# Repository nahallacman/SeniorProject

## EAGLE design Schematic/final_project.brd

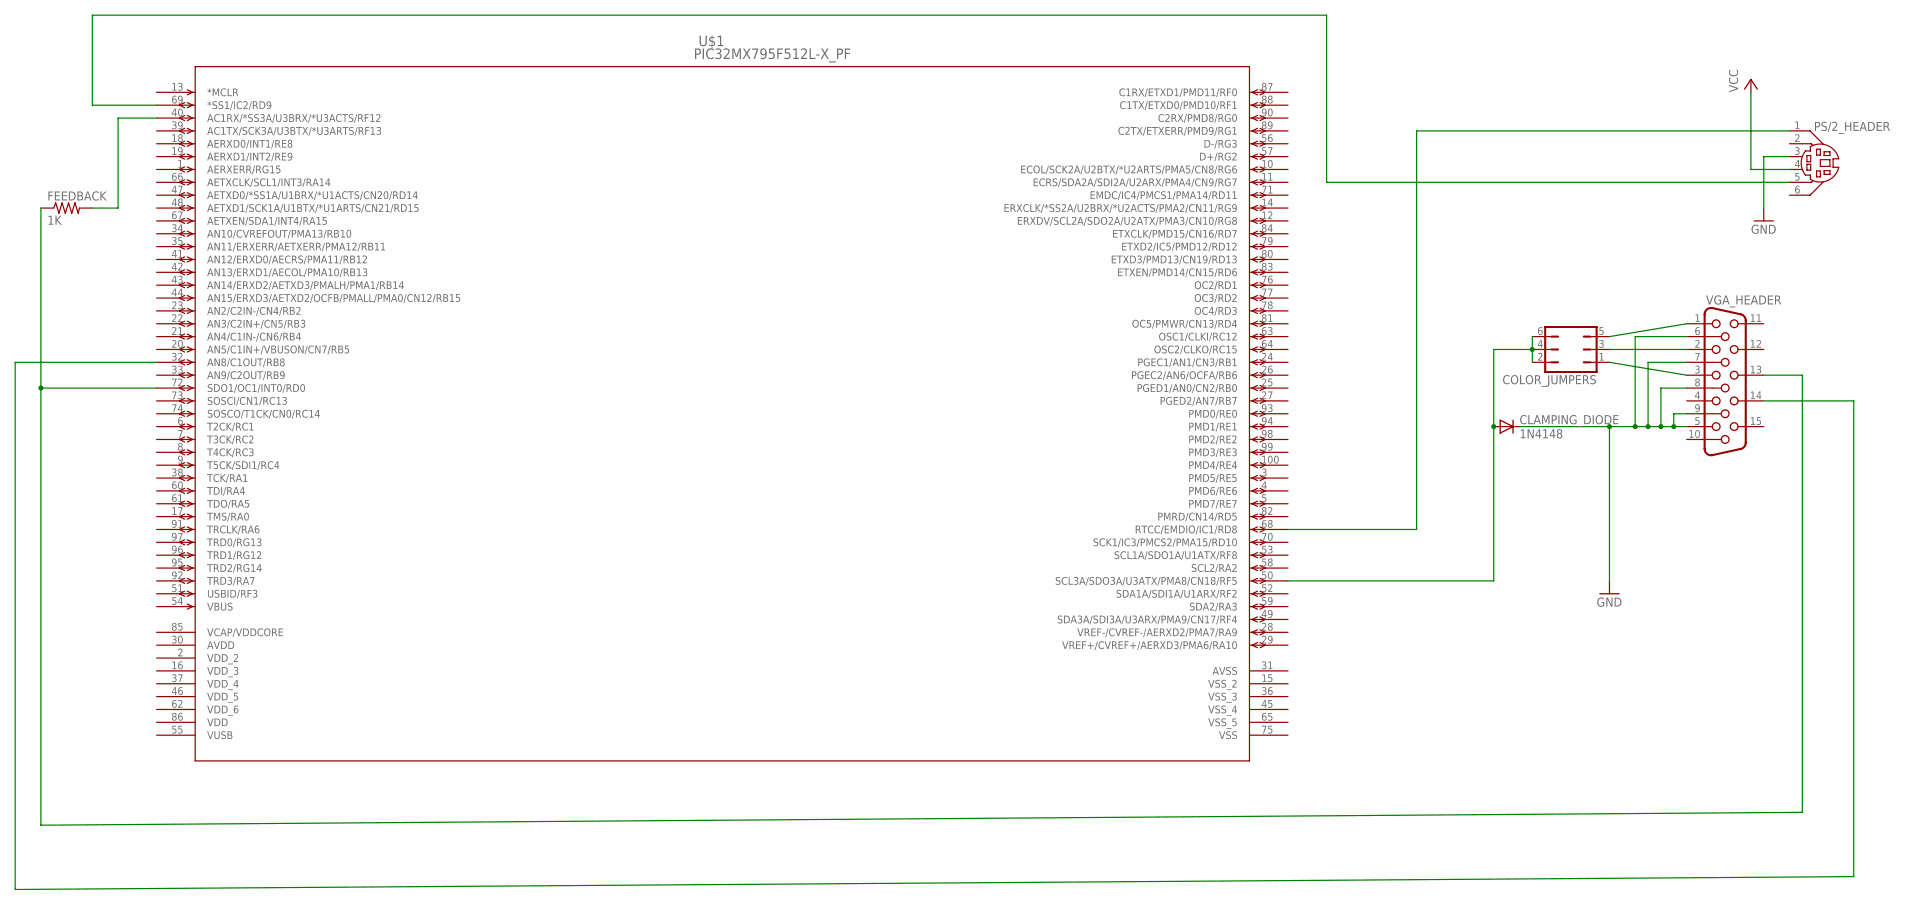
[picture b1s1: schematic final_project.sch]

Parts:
CLAMPING_DIODE: 1N4148; DO41-10
COLOR_JUMPERS: JP3Q
FEEDBACK: 1K; 0204V
PS/2_HEADER: MDIN06K
U$1: PIC32MX795F512L-X_PF; TQFP100_14X14MC
VGA_HEADER: HF15H; HDF15H

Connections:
AVDD: U$1.30 (AVDD)
AVSS: U$1.31 (AVSS)
GND: CLAMPING_DIODE.C, PS/2_HEADER.3, VGA_HEADER.5, VGA_HEADER.6, VGA_HEADER.7, VGA_HEADER.8, VGA_HEADER.9
unnamed: COLOR_JUMPERS.5, VGA_HEADER.1
unnamed: COLOR_JUMPERS.3, VGA_HEADER.2
unnamed: COLOR_JUMPERS.1, VGA_HEADER.3
unnamed: CLAMPING_DIODE.A, COLOR_JUMPERS.2, COLOR_JUMPERS.4, COLOR_JUMPERS.6, U$1.50 (SCL3A/SDO3A/U3ATX/PMA8/CN18/RF5)
unnamed: U$1.32 (AN8/C1OUT/RB8), VGA_HEADER.14
unnamed: FEEDBACK.1, VGA_HEADER.13
unnamed: PS/2_HEADER.1, U$1.68 (RTCC/EMDIO/IC1/RD8)
unnamed: PS/2_HEADER.5, U$1.69 (*SS1/IC2/RD9)
unnamed: FEEDBACK.2, U$1.40 (AC1RX/*SS3A/U3BRX/*U3ACTS/RF12)
VCAP/VDDCORE: U$1.85 (VCAP/VDDCORE)
VCC: PS/2_HEADER.4
VDD: U$1.86 (VDD)
VDD_2: U$1.2 (VDD_2)
VDD_3: U$1.16 (VDD_3)
VDD_4: U$1.37 (VDD_4)
VDD_5: U$1.46 (VDD_5)
VDD_6: U$1.62 (VDD_6)
VSS: U$1.75 (VSS)
VSS_2: U$1.15 (VSS_2)
VSS_3: U$1.36 (VSS_3)
VSS_4: U$1.45 (VSS_4)
VSS_5: U$1.65 (VSS_5)
VUSB: U$1.55 (VUSB)

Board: 2 copper layers, 6 parts (0 on the bottom side), 10 nets, no tracks yet.

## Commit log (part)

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2014-09-14 :circus_tent: Added .gitattributes & .gitignore files
2014-09-21 TCP client and server demos working
2014-10-27 Keyboard demo working
    Keyboard shows clock state change using breakpoints, demonstrates that
    the keyboard is sending a clock signal.
2014-11-15 Testing variation 2
    Got the screen to blink on and off while trying, probably closer to the
    correct timing. To get any other real meaningful changes I will probably
    need a logic analyzer or an oscilloscope. Probably the oscilloscope for
    the levels I am using, .7 volts is VGA standard.
2014-11-16 small edits
2014-11-25 Quick ISR rewrite
    Not tested. Left old test file as oldmain.c, replaced the main,c with a
    new one with ISR's in it.
2014-11-25 ISR's working, needs testing
2014-11-26 self modifying ISR's
2014-12-12 Working Senior Project Demo
    Begins by displaying a single line on screen. On any key press it
    changes to display 3 lines.
2014-12-18 More configuration tinkering
    Still can't get the SPI interrupt to fire correctly, probably need to
    find the exact documentation for my processor.
2014-12-18 more testing
    trying to get SPI to transmit, can't seem to get that to happen, but now
    the interrupt properly happens at least,.
2014-12-19 Alright solid lines
    H-sync is still off, not sure what the actual resolution being displayed
    is.
2014-12-20 Much more solid lines
    Not perfect yet, but the lines are no longer incredibly shaky.
2014-12-20 most solid lines so far
    but not quite complete.
2014-12-20 minor testing
    Hardware may be causing current sourcing problems, all 5's don't display
    properly.
2014-12-26 writechar() works minimally
    writechar() is able to take an 8 character array and display it over 8
    lines while taking an x and y co-ordinate. The y co-ordinate is exact,
    but the x co-ordinate only rounds to 32 bit numbers which needs to be
    fixed.
2014-12-26 Cleaned up main.c
    Put several items into the VGA.c/.h files where they belong, system
    confirmed to still work.
2015-01-12 Change Notification Interrupt works
    The interrupt fires correctly, but the ISR doesn't properly read the key
    press.
2015-01-19 Keyboard Scan Code Buffer works
    Multiple key presses and releases are confirmed working and values are
    correctly written into the buffer.
2015-01-19 Messing with writechar()
    Still doesn't work correctly. Will attempt again another day.
2015-01-20 Tied key presses to printing
    Took a bit of messing with things and using an external variable to tell
    the system when a keypress is ready to be processed. Screen will change
    when a key is pressed on the keyboard.
2015-01-20 Added a few characters to be translated
    will now print "q w e r t y"
2015-01-24 Added most of the normal keys.
    They all print, every character that is implemented currently is:
    `1234567890-=qwertyuiop[]\asdfghjkl;'zxcvbnm,./
    Still needed are F# keys, num pad keys, modifier keys, arrow keys, ect.
2015-01-28 Laptop Updates
2015-01-30 testing
2015-01-31 Fixed screen garbage!
    writechar() has been fixed, screen correctly prints all characters now.
2015-01-31 Added descriptive comments about future work
2015-02-01 Added ShiftScreenDown() to VGA.c
    Now I have a screen that scrolls up and and down, next I might go for
    right or left, even though that is not as important. Going to put that
    into the maybe category.
2015-02-02 Added basic Caps Lock functionality
    Caps lock inverts shift on/off. Left shift turns shift on, right shift
    turns shift off. Also added all the ~!@#$%^&*()_+ symbols to be printed.
2015-02-05 Added line input base and cursor limiting
    Added a new function placeChar() to wrap writechar() and control where
    things are on the screen. Needs work with the line in the cases of
    having text before the line starts, and accumulating the line. A good
    way to do accumulation is fill the line buffer, then copy it when you
    hit enter.
2015-02-08 Moved PS/2 to other port pins
    Now using input comparator 2 for PS/2.
2015-02-18 comment fix and added pictures
2015-02-27 Got the Ethernet starter kit working
    Got it working with a python demo that prints the text that it receives
    from a single source. Tested from other computers and the same computer
    using putty. Doesn't currently work from same computer, only the name
    192.168.11.57 so make sure to change that if you can't get listening
    working.
2015-03-03 editor changes
2015-03-03 Made text send over TCP/IP!!!!1
    It sends text, but at the end of a keypress( not too sure why).
    Regardless, I am able to enter in text on a keyboard, display it on a
    screen, and send it over TCP/IP, the three major goals in my project.
2015-03-04 Altered escape, clears screen, resets cursor
2015-03-07 Added PS2.c updates
    Forgot to add those.
2015-03-07 Finished the __Microcontroller defines
    Should keep the test code base and the pic32 only code base separate
    now.
2015-03-07 Changed the includes, needs to be tested
2015-03-07 Problems with default global values
    Need to alter all of the code to remove default global values, but it
    should be done incrementally. Going to test these changes so far then
    add more changes.
2015-03-07 Few alterations, working on hardware
2015-03-08 Tried hard links fixes.
    Seems to have worked. Will see if it sustains.
2015-03-08 Tested and fixed on the pic32
2015-03-08 Tested the hard linking again, doesn't work
    All of the hard links I made don't work now. Super annoying.
2015-03-08 Moved some more defines to appropriate places
2015-03-08 Fixed problems tested working on pic32
2015-03-08 Another issue involving the signed-ness of chars.
    In some places I have unsigned chars and some place I just have chars.
    The best type for them should probably be unsigned 8 bit ints. uint8_t
    is the type.
2015-03-08 Still having an issue with unity
    Can't make the external functions work correctly. Fails to build the
    test environment still.
2015-03-09 Merge branches
    fixed everything I think, readded the VGA.c to EthKitTCP\Dev\ and now I
    need to make sure nothing broke with the merge for running code on other
    computers.
2015-03-09 Fixed a few issues
    Got cross file compile working (forgot an include in the test file). I
    also found that _bswapw() may not be standard and I may have to make a
    workaround for desktop processors.
2015-03-09 Testing project compiles!!!!!!!!!
    Now it should be relatively easy to create a better testing environment.
2015-03-10 Made the bitmap int indexed
    It is easy to change the index part I realize now, I just need to do a
    (type *) cast and be careful with my boundaries.
2015-03-10 Corrected text printing to the bitmap
2015-03-10 Small updates
    testKeyboardAgitator still doesnt work right, it clears the screen when
    we use esc, but doesn't print the numbers 1 2 or 3 in a basic test.
2015-03-11 Completed one test, almost finished another
    Finished testKeyboardLookup and did a large portion of
    testTranslateKeypress.
2015-03-11 Command interprets on hardware
    Still having issues on making things play nice in the unity test
    environment.
2015-03-11 Fixed and added some tests
    Still could really use a file comparator command. Should be pretty easy,
    just get 2 file pointers and byte wise compare them.
2015-03-14 Prepared Demo, removed some extra code.
    This is the demo for the 3/14/15 presentation.
2015-03-18 After in demo changes
2015-03-28 Added final turn in for testing class.
2015-03-28 Tried some things. no success
    Should really try to do it with just a 3x3 array of characters to make
    things easy.
2015-04-05 Confirmed everything working over wifi network
2015-04-06 added CompareTextLines(void)
    altered another couple functions too
2015-04-06 Merge remote-tracking branch 'origin/master'
    Conflicts:
    EthKitTCP/TCPIP/CodeFromMicrochip/MPLAB.X/.map
    EthKitTCP/TCPIP/CodeFromMicrochip/MPLAB.X/build/XC32-PIC32_ETH_SK_ETH795/debug/_ext/1386482886/PS2.o
    EthKitTCP/TCPIP/CodeFromMicrochip/MPLAB.X/build/XC32-PIC32_ETH_SK_ETH795/debug/_ext/1472/CustomHTTPApp.o
2015-04-06 .o files from compiling
2015-04-06 Trying to fix project issues.
2015-04-06 If you close MPLABX make sure to commit IMMEDIATELY
2015-04-06 closed MPLABX
2015-04-10 not sure what changed, syncing git
2015-04-17 tried to work on clearchar()
    does clear the text, but needs to reprint the text that is supposed to
    be there.
2015-04-18 clearchar() tested moderately
2015-04-18 exit mplab
2015-04-18 Small changes.
2015-04-18 closed mplab
2015-04-29 gave different target address
2015-05-08 added doxygen
2015-05-10 More refactoring.
    Delete doesn't work.
2015-05-10 more doxygen graph updates.
2015-05-10 close mplab and run doxygen
2015-05-11 Added a copy of the project report
    Not sure if it is the right one but it has some diagrams I need.
2015-05-12 Added vga signal format picture
2015-05-12 Added a command, and printstring()
2015-05-12 closing mplab
2015-05-13 successfully removed the textlineindex
    It was unnecessary and was confusing things with more than one cursor.
2015-05-13 Added \n interpretation
    When a \n key is printed now, the system sends the text to the next
    line. Found a printing bug where the ends of lines are not on the right
    character.
2015-05-14 System can now print a command and keep going
    I haven't tested deleting off the end of the typed area, but it appears
    to work pretty well so far. Can print the help command multiple times.
2015-05-14 Partially fixed backspace
    Now works normally over all 4 characters positions, but there are still
    bugs when it gets near the beginning of the line.
2015-05-14 comment and doxygen update
2015-05-14 Edited unity copy script. Unity tests need work.
    Now it copies the cursor.c and cursor.h files as well as the others.
    Unity tests still need a lot of code updates to work properly.
2015-05-15 Redid some stuff to make testing work again.
    Did a doxygen update too. Don't forget to add the source header files to
    the test file in Unity!!
2015-05-15 All test pass.
    Need to add more tests.
2015-05-17 Got TCP/IP communication working!!!!
    Need to create some functionality to smooth out the communications, but
    it actually works!
2015-05-17 Got a dir print to work perfectly!
2015-05-18 Added a multi stage test for backspace functions.
2015-05-18 Forgot to save file.
2015-05-25 Messing with stuff, may have broke commands
2015-05-28 Added a python TCP client.
    Will be a good standard to try and emulate on the PIC32. May have to
    write another client to do the whole disconnect and reconnect patterns.
    Also could use try and catch blocks in the python code.
2015-05-30 Making local variable unique.
2015-05-30 close visual studio
2015-06-01 Doxygen and test update
    Didn't do much, just checked if things passed.
2015-06-02 testing internet
